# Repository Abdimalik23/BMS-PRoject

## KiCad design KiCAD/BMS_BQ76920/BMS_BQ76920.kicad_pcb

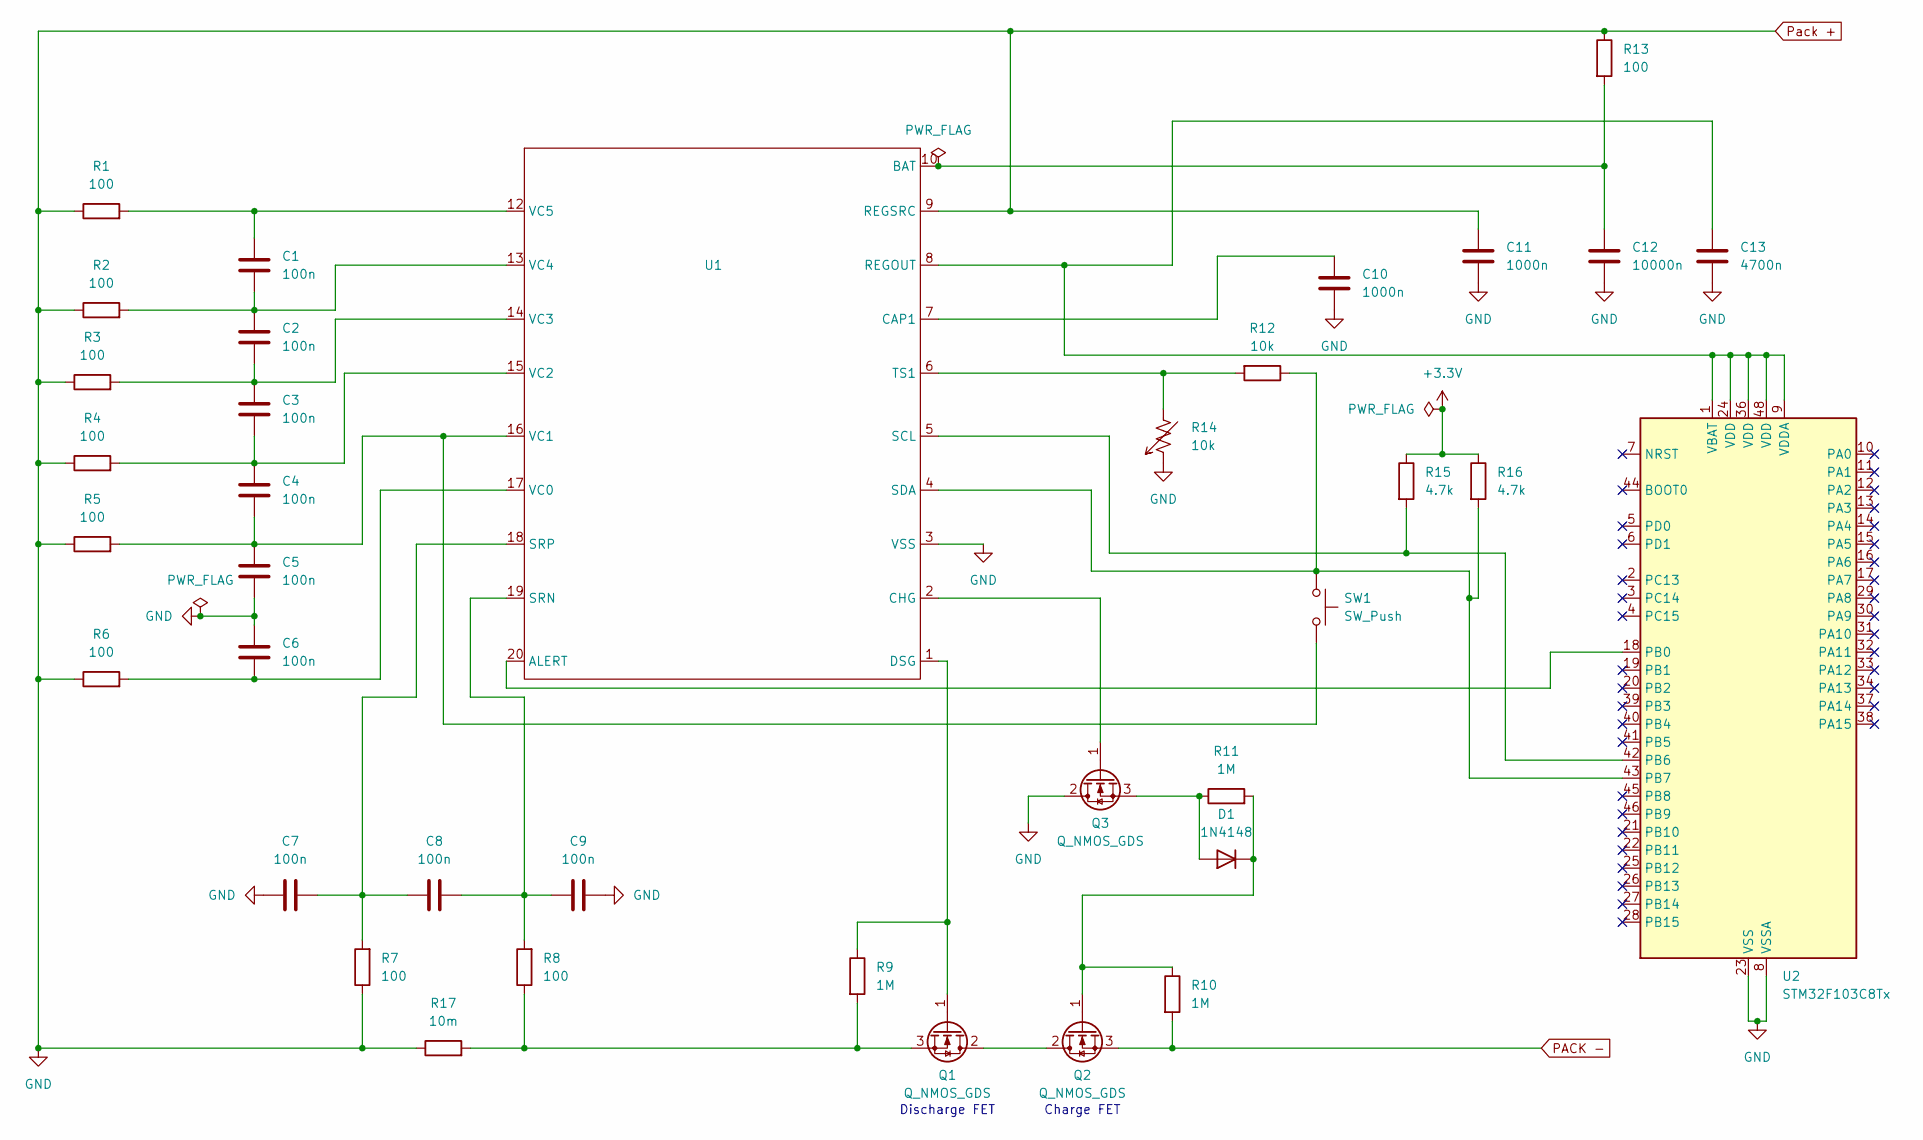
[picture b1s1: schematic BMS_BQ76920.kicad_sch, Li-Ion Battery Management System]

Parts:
C1, C2, C3, C4, C5, C6, C7, C8, C9: 100n; C_0805_2012Metric
C10, C11: 1000n; C_0805_2012Metric
C12: 10000n; C_0805_2012Metric
C13: 4700n; C_0805_2012Metric
D1: 1N4148; D_SOD-123
Q1, Q2, Q3: Q_NMOS_GDS; TSOT-23_HandSoldering
R1, R2, R3, R4, R5, R6, R7, R8, R13: 100; R_0805_2012Metric
R9, R10, R11: 1M; R_0805_2012Metric
R12, R14: 10k; R_0805_2012Metric
R15, R16: 4.7k; R_0805_2012Metric
R17: 10m; R_0805_2012Metric
SW1: SW_Push; SW_PUSH_6mm_H4.3mm
U1: TSSOP-20_4.4x6.5mm_P0.65mm
U2: STM32F103C8Tx; LQFP-48_7x7mm_P0.5mm

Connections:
+3.3V: R15.1, R16.1
unnamed: D1.2 (A), Q3.3 (S), R11.1
unnamed: D1.1 (K), Q2.1 (G), R10.1, R11.2
unnamed: Q1.2 (D), Q2.2 (D)
unnamed: Q1.1 (G), R9.1, U1.1 (DSG)
unnamed: Q1.3 (S), R8.1, R9.2, R17.2
unnamed: Q3.1 (G), U1.2 (CHG)
unnamed: U1.20 (ALERT), U2.18 (PB0)
unnamed: C12.2, R13.2, U1.10 (BAT)
unnamed: C10.2, U1.7 (CAP1)
unnamed: C13.2, U1.8 (REGOUT), U2.1 (VBAT), U2.9 (VDDA), U2.24 (VDD), U2.36 (VDD), U2.48 (VDD)
unnamed: R15.2, U1.5 (SCL), U2.42 (PB6)
unnamed: R12.1, R16.2, SW1.1, U1.4 (SDA), U2.43 (PB7)
unnamed: C8.2, C9.1, R8.2, U1.19 (SRN)
unnamed: C7.2, C8.1, R7.2, U1.18 (SRP)
unnamed: R12.2, R14.2, U1.6 (TS1)
unnamed: C6.2, R6.2, U1.17 (VC0)
unnamed: C4.2, C5.1, R5.2, SW1.2, U1.16 (VC1)
unnamed: C3.2, C4.1, R4.2, U1.15 (VC2)
unnamed: C2.2, C3.1, R3.2, U1.14 (VC3)
unnamed: C1.2, C2.1, R2.2, U1.13 (VC4)
unnamed: C1.1, R1.2, U1.12 (VC5)
PACK -: Q2.3 (S), R10.2
Pack +: C5.2, C6.1, C7.1, C9.2, C10.1, C11.1, C11.2, C12.1, C13.1, Q3.2 (D), R1.1, R2.1, R3.1, R4.1, R5.1, R6.1, R7.1, R13.1, R14.1, R17.1, U1.3 (VSS), U1.9 (REGSRC), U2.8 (VSSA), U2.23 (VSS), U2.35 (VSS), U2.47 (VSS)

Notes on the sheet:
Charge FET
Discharge FET

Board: 2 copper layers, 37 parts (0 on the bottom side), 24 nets, no tracks yet.

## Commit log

2026-05-16 Add MOSFETs Q1 Q2 and shunt resistor Rsns to schematic
2026-05-16 Arrange power path - Q1 Q2 Rsns correct orientation and layout
2026-05-17 fixing symbol mistakes
2026-05-17 Place all schematic components - ready for wiring
2026-05-17 Schematic complete - ERC passed with zero errors
2026-05-18 All llaidout pcb editor
